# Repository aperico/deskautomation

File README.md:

# Automated Mechanical Desk Lift System

## Quick Start

### Automated Development Pipeline (Recommended)

The fastest way to build and test the project:

```bash
# Complete pipeline: build + dual motor validation + static analysis
python toolchain/run-pipeline.py all

# Build only
python toolchain/run-pipeline.py clean-build

# Run tests (validates both MT_BASIC and MT_ROBUST motor types)
python toolchain/run-pipeline.py test

# Quick unit test during development
python toolchain/run-pipeline.py unit

# Get help
python toolchain/run-pipeline.py help
```

**📖 Detailed Instructions:**
- **Pipeline Guide:** [toolchain/README.md](toolchain/README.md) - Complete pipeline manual
- **Build Guide:** [src/README.md](src/README.md) - Manual build and test instructions
- **Test Overview:** [tests/README.md](tests/README.md) - Test suite quick reference

---

## Project Overview

The Automated Mechanical Desk Lift System is a motorized solution for height-adjustable desks, enabling users to easily switch between sitting and standing positions. The system features responsive controls, safety mechanisms to prevent accidents, and reliable operation over the product lifetime. Key features include:
- **Configurable motor drivers:** Support for both L298N (cost-optimized) and IBT_2 (high-capacity) motor controllers
- Motorized height adjustment from 30 cm to 120 cm
- Support for up to 20 kg load (monitor, keyboard, etc.)
- UP/DOWN buttons for intuitive control
- Immediate halt on button release or obstruction detection
- Robust safety features including limit sensors and current sensing for jam detection
- Smooth, predictable motion for user comfort
- Designed for office environments to improve health and productivity
- Modular architecture for maintainability and future feature expansion
- Comprehensive documentation and testing to ensure quality and reliability
- Open-source hardware and software design for community collaboration and innovation

### Motor Driver Options

The system supports two motor driver configurations, selectable at compile-time:

| Driver | Model | Cost | Capacity | Use Case |
|--------|-------|------|----------|----------|
| **MT_BASIC** | L298N Dual H-Bridge | Low (~$2-5) | Standard (~50kg) | Cost-optimized office desks |
| **MT_ROBUST** | IBT_2 Intelligent Driver | Moderate (~$10-15) | High (~100kg+) | Heavy-duty commercial desks |

Both drivers share the same software (unified HAL interface) and provide equivalent safety and functionality. See [Motor Driver Configuration Guide](documentation/07_MotorDriverConfiguration.md) for build and switching instructions.

## Motor Configuration Architecture

The system implements a robust motor configuration encapsulation pattern to support multiple motor driver types:

### Design Approach

- **Compile-Time Configuration (Current)**: Motor type is defined at compile-time in `src/motor_config.cpp` with validation
- **Runtime-Ready (Future)**: Architecture is prepared for NVM-based runtime configuration without code changes
- **Encapsulation Interface**: `MotorConfig_getMotorType()` function provides the sole accessor for motor configuration
- **Application Transparency**: All application logic is motor-type-agnostic; HAL layer handles driver-specific details

### Configuration Files

| File | Role | Details |
|------|------|---------|
| `src/motor_config.h` | Public interface | Type definitions, feature documentation, function declaration |
| `src/motor_config.cpp` | Private implementation | MOTOR_TYPE macro, validation, getter function, NVM migration comments |

### Switching Motor Drivers

```bash
# Default: MT_BASIC (L298N)
cmake -S . -B build && cmake --build build

# To use MT_ROBUST (IBT_2): Edit src/motor_config.cpp line 44
# #define MOTOR_TYPE MT_BASIC        <- Change to MT_ROBUST
# Then rebuild:
cmake --build build
```

### Test Coverage

All 37 unit and integration tests validate both motor configurations:
- **MT_BASIC**: L298N driver (default)
- **MT_ROBUST**: IBT_2 driver

Tests can be run against either driver by changing the MOTOR_TYPE definition. See [05_SoftwareArchitecture.md](documentation/05_SoftwareArchitecture.md) (AD-009: Motor Configuration Encapsulation) and [06_00_DetailedDesign.md](documentation/06_00_DetailedDesign.md) (Motor Configuration Module) for detailed technical documentation.

---

## Documentation Index

### Development Guidelines

| Document | Description |
|----------|-------------|
| [toolchain/coding_guides_and_checks.md](toolchain/coding_guides_and_checks.md) | **⚠️ Coding standards for safety-critical code (NASA Power of Ten, MISRA C:2012, ISO 25119)** |
| [toolchain/README.md](toolchain/README.md) | Development pipeline and automated testing guide |
| [toolchain/ARCHITECTURE.md](toolchain/ARCHITECTURE.md) | Pipeline architecture and design details |

### Requirements and Design

| Document | Description |
|----------|-------------|
| [01_MissionStatement.md](documentation/01_MissionStatement.md) | Project mission and overall purpose |
| [01_SystemObjectives.md](documentation/01_SystemObjectives.md) | High-level system objectives and goals |
| [02_ConceptOfOperations.md](documentation/02_ConceptOfOperations.md) | Operational concept and use cases |
| [02_01_HARA-prep.md](documentation/02_01_HARA-prep.md) | HARA preparation (draft) |
| [02_02_HARA-complete.md](documentation/02_02_HARA-complete.md) | Hazard analysis and risk assessment (HARA) |
| [02_03_SafetyGoals.md](documentation/02_03_SafetyGoals.md) | Safety goals derived from HARA |
| [03_00_SystemRequirements.md](documentation/03_00_SystemRequirements.md) | System-level requirements specification |
| [03_01_SystemArchitecture.md](documentation/03_01_SystemArchitecture.md) | System architecture and interfaces |
| [03_01_01_TechnicalSafetyConcept.md](documentation/03_01_01_TechnicalSafetyConcept.md) | Technical safety concept |
| [03_02_RequirementsTraceabilityMatrix.md](documentation/03_02_RequirementsTraceabilityMatrix.md) | Requirements traceability matrix |
| [04_SoftwareRequirements.md](documentation/04_SoftwareRequirements.md) | Software requirements and functional specifications |
| [04_01_SoftwareVerificationSpecification.md](documentation/04_01_SoftwareVerificationSpecification.md) | Software test specifications and verification methods |
| [05_SoftwareArchitecture.md](documentation/05_SoftwareArchitecture.md) | Software architecture design and component structure |
| [06_00_DetailedDesign.md](documentation/06_00_DetailedDesign.md) | Detailed software design and implementation details |
| [06_01_DetailedDesign_InteractionDiagrams.md](documentation/06_01_DetailedDesign_InteractionDiagrams.md) | Sequence diagrams and data flow visualizations |
| [07_MotorDriverConfiguration.md](documentation/07_MotorDriverConfiguration.md) | Motor driver configuration guide (L298N vs IBT_2)
| [10_SystemTestSpecification.md](documentation/10_SystemTestSpecification.md) | System test plan and test specifications |
| [10_01_SystemTestReport.md](documentation/10_01_SystemTestReport.md) | System test report and results |
| [11_HardwareDocumentation.md](documentation/11_HardwareDocumentation.md) | Hardware components and wiring documentation |
| [02_ConceptOfOperations_Reviews.md](documentation/02_ConceptOfOperations_Reviews.md) | ConOps review protocol and records |
| [03_00_SystemRequirements_Reviews.md](documentation/03_00_SystemRequirements_Reviews.md) | System requirements review protocol and records |
| [03_01_01_TechnicalSafetyConcept_Reviews.md](documentation/03_01_01_TechnicalSafetyConcept_Reviews.md) | Technical safety concept review protocol and records |
| [03_01_SystemArchitecture_Reviews.md](documentation/03_01_SystemArchitecture_Reviews.md) | System architecture review protocol and records |
| [04_SoftwareRequirements_Reviews.md](documentation/04_SoftwareRequirements_Reviews.md) | Software requirements review protocol and records |
| [05_SoftwareArchitecture_Reviews.md](documentation/05_SoftwareArchitecture_Reviews.md) | Software architecture review protocol and records |
| [06_DetailedDesign_Reviews.md](documentation/06_DetailedDesign_Reviews.md) | Detailed design review protocol and records |
| [10_SystemTestSpecification_Reviews.md](documentation/10_SystemTestSpecification_Reviews.md) | System test specification review protocol and records |
| [feature-pdrs/](documentation/feature-pdrs/) | System feature concept reviews |

## Project Structure

### Root Directory

| File/Directory | Description |
|----------------|-------------|
| `CMakeLists.txt` | CMake build configuration file |
| `CMakePresets.json` | CMake preset configurations |
| `README.md` | Project overview and instructions (this file) |
| `.github/` | GitHub workflows and CI/CD configuration |

### Source Code (`src/`)

| File | Description |
|------|-------------|
| `desk_app.cpp/h` | Main application logic and state machine |
| `desk_types.h` | Type definitions and data structures |
| `hal.cpp/h` | Hardware Abstraction Layer (HAL) interface |
| `motor_config.h` | Motor driver type configuration (MT_BASIC or MT_ROBUST) |
| `motor_controller.cpp/h` | Motor control logic and algorithms |
| `pin_config.h` | Arduino pin assignments (configurable per motor type) |
| `src.ino` | Arduino firmware entry point |

### Tests (`tests/`)

| File | Description |
|------|-------------|
| `UnitTests.cpp` | Unit tests for individual functions and classes |
| `ComponentTests.cpp` | Component-level integration tests |
| `IntegrationTests.cpp` | Full system integration tests |
| `hal_mock/` | Mock implementations of HAL for testing on host |
| `└── HALMock.cpp/h` | Mock HAL implementation |
| `└── SerialMock.cpp/h` | Mock Serial communication for testing |

### Training Materials (`00_training_context/`)

| File | Description |
|------|-------------|
| `00_agenda.md` | Training overview and agenda |
| `01_hello-world.md` | Getting started guide |
| `02_aisetup.md` | AI/Copilot setup instructions |
| `03_prompting-techniques.md` | AI prompting best practices |
| `04_00_deskautomation-syseng.md` | Systems engineering overview |
| `04_01_00_system-definition.md` | System definition guide |
| `04_01_01_system-definition-architecture.md` | Architecture definition guide |
| `04_02_software-construction.md` | Software construction practices |
| `04_03_00_component-verification.md` | Component testing guide |
| `04_03_01_software_integration-verification.md` | Integration testing guide |
| `04_03_03_system-testing.md` | System testing guide |
| `05_traceability-matrix.md` | Requirements traceability |
| `06_workflow-pipelines.md` | CI/CD pipeline documentation |
| `07_process-assessment.md` | Process quality assessment |

### Schematics (`schematics/`)

| Directory | Description |
|-----------|-------------|
| `schmatics_desk_automation/` | KiCad project files for desk automation |
| `└── DeskAutomation_MotorControl/` | Motor control circuit schematics |
| `└── DeskAutomation.pretty/` | Custom KiCad footprints |

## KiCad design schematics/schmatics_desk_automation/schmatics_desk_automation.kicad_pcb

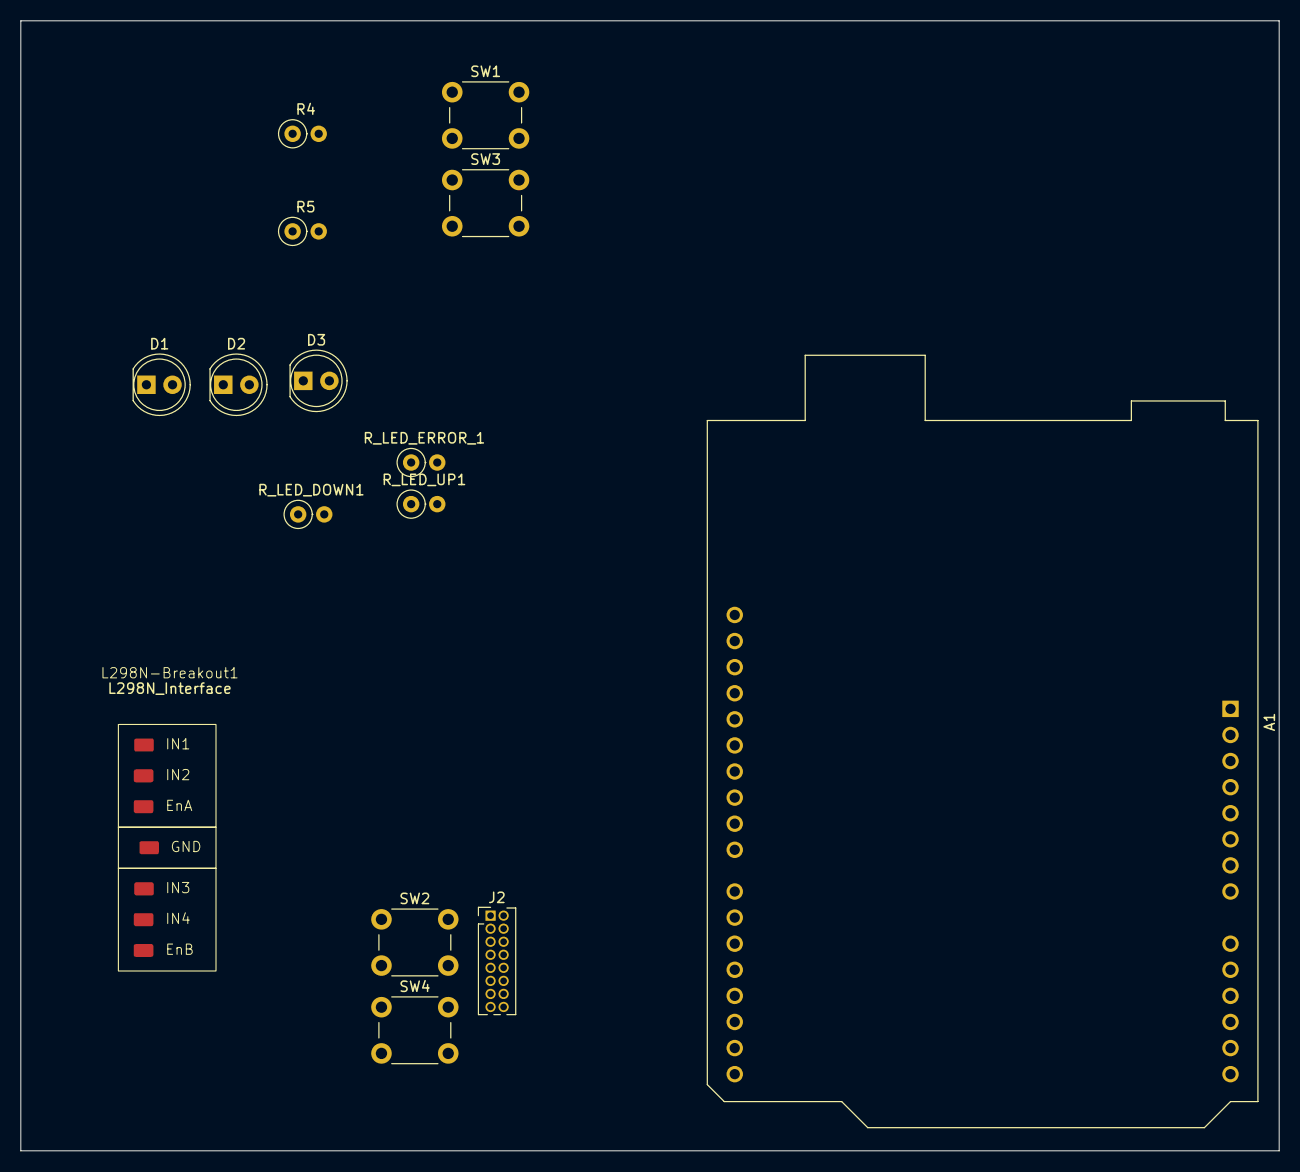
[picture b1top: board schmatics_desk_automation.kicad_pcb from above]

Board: 2 copper layers, 122.5 x 110.0 mm, 15 parts (0 on the bottom side), 16 nets, no tracks yet.

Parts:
A1: Arduino_UNO_R3
D1: LED_DOWN; LED_D5.0mm
D2: LED UP; LED_D5.0mm
D3: ERROR_LED; LED_D5.0mm
J2: Conn_01x15_MountingPin; PinHeader_2x08_P1.27mm_Vertical
L298N-Breakout1: L298N_Interface; L298N Interface
R4, R5: 330; R_Axial_DIN0207_L6.3mm_D2.5mm_P2.54mm_Vertical
R_LED_DOWN1: 330; R_Axial_DIN0207_L6.3mm_D2.5mm_P2.54mm_Vertical
R_LED_ERROR_1: 330; R_Axial_DIN0207_L6.3mm_D2.5mm_P2.54mm_Vertical
R_LED_UP1: 330; R_Axial_DIN0207_L6.3mm_D2.5mm_P2.54mm_Vertical
SW1: BT_UP; SW_PUSH_6mm_H5mm
SW2: Lower Limit; SW_PUSH_6mm_H5mm
SW3: BT_DOWN; SW_PUSH_6mm_H5mm
SW4: Uppr Limit; SW_PUSH_6mm_H5mm

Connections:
Button DOWN: A1.18 (D3), J2.8, SW3.1
Button UP: A1.17 (D2), J2.9, SW1.1
GND: D1.2 (A), D2.2 (A), D3.2 (A), J2.1, J2.2, L298N-Breakout1.4, R4.2, R5.2, R_LED_ERROR_1.1, SW2.2, SW4.2
LED_DOWN: A1.25 (D10), J2.4, R_LED_DOWN1.1
LED_ERROR: A1.7 (GND), A1.28 (D13)
LED_UP: A1.26 (D11), J2.3, R_LED_UP1.1
Lower Limit: J2.10, SW2.1
Motor DIR CTRL 1: A1.20 (D5), J2.7, L298N-Breakout1.1
Motor DIR CTRL 2: A1.21 (D6), J2.6, L298N-Breakout1.2
Motor PWM: A1.24 (D9), J2.5, L298N-Breakout1.3
unnamed: D1.1 (K), R_LED_DOWN1.2
unnamed: D2.1 (K), R_LED_UP1.2
unnamed: D3.1 (K), R_LED_ERROR_1.2
unnamed: R4.1, SW1.2
unnamed: R5.1, SW3.2
Uppler Limit: J2.11, SW4.1

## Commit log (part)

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2025-12-29 feat: Implement initial application logic, state machine, and hardware abstraction layer for desk automation.
2025-12-29 feat: Establish initial project structure, CMake build system, HAL, desk controller logic, and Google Test setup.
2025-12-29 feat: Initialize application state and enhance HAL with state processing for desk automation
2025-12-29 chore: Remove obsolete InstallationLog.txt file
2025-12-30 feat: Refactor HAL and PinConfig for improved LED handling and state management
2025-12-30 feat: Revise README for improved clarity, structure, and detail on system architecture and use cases
2026-01-06 Implement enhanced error handling and dual button logic in DeskController
    - Added error state handling for simultaneous activation of both upper and lower limits.
    - Implemented emergency stop logic when moving up or down while a limit is active.
    - Updated button press logic to prevent movement when both UP and DOWN buttons are pressed.
    - Enhanced unit tests to cover new error handling scenarios and button press logic.
    - Removed redundant code and improved readability in DeskController and unit tests.
2026-01-07 Refactor documentation: Remove Software Requirements, add new files for Glossary, Hardware Connections, Roadmap, Safety Notes, Software Architecture, Software Detailed Design, Software Test Cases Spe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
    - Deleted SoftwareRequirements.md and replaced with a new version.
    - Introduced Glossary.md to define key terms.
    - Added HardwareConnections.md for pin assignments.
    - Created Roadmap.md outlining planned enhancements.
    - Included SafetyNotes.md for safety precautions.
    - Developed SoftwareArchitecture.md detailing system structure.
2026-01-07 Refactor documentation: Revise README, enhance safety notes, and update glossary, hardware connections, roadmap, and software architecture for clarity and completeness
2026-01-07 Refactor documentation: Update navigation links and enhance glossary for improved clarity and organization
2026-01-07 Refactor documentation: Enhance README with a glossary and improve navigation in Software Architecture and Software Detailed Design for clarity and organization
2026-01-07 Refactor documentation: Consolidate glossary content into README, update hardware connections references, and enhance compliance details across multiple documents for clarity and consistency
2026-01-07 Refactor README and add ASPICE Assessment: Enhance documentation index with detailed descriptions and introduce a comprehensive ASPICE assessment checklist for improved compliance tracking and clarit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
2026-01-07 Refactor ASPICE Assessment: Add introductory section for overall maturity classification to enhance clarity and context for compliance evaluation.
2026-01-07 Refactor README: Remove outdated documentation index and streamline ASPICE maturity level description for improved clarity and focus.
2026-01-07 Refactor README: Add documentation index with links and descriptions for improved navigation and clarity
2026-01-07 Add desk crank image to README for enhanced visual representation
2026-01-07 Refactor CI workflow: Clean up GoogleTest installation steps for improved clarity
2026-01-07 Enhance CI workflow: Add Cppcheck linting step and report upload for improved code quality
2026-01-07 Refactor CI workflow: Update coverage report generation to use geninfo for improved accuracy
2026-01-07 Fix image file extension in README.md for correct display
2026-01-07 Fix unit test output handling in CI workflow to correctly generate JUnit XML report
2026-01-07 Refactor Software Detailed Design and System Use Cases
    - Updated Software Detailed Design document for clarity and consistency, including improved formatting and organization of sections.
    - Enhanced module decomposition details and added comprehensive descriptions for each module.
    - Revised System Use Cases to include a new use case diagram and detailed flows for each use case, ensuring alignment with the updated design.
    - Improved error handling and safety features in use cases, emphasizing user interactions and system responses.
    - Added functional coverage map linking core functions to relevant use cases.
    - Made minor adjustments to the main Arduino file to ensure proper static declaration
2026-01-07 Enhance integration testing framework: Add IntegrationTests.cpp, improve HAL mock implementations, and update documentation for test specifications and traceability matrix.
2026-01-07 Refactor CI workflow: Update test execution to run only Unit and Integration labelled tests, and adjust result file naming for clarity.
2026-01-07 Update ASPICE maturity assessment: Revise document structure, enhance clarity, and update evaluation results and action plans.
2026-01-07 Enhance System Use Cases Documentation
    - Updated document version to 1.1 and added last updated date, status, author, and reviewers.
    - Added an overview section to clarify the purpose of the document.
    - Introduced a use case summary table for quick reference of all use cases, including ID, name, priority, frequency, status, and related requirements.
    - Expanded individual use cases (UC-01 to UC-08) with detailed descriptions, triggers, preconditions, main flows, alternative flows, exception flows, postconditions, related requirements, and test ca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
    - Improved formatting for better readability and adherence to IEEE 29148-2018 standard.
2026-01-07 feat: Implement movement timeout and enhance state management
    - Added movement timeout functionality (SWE-REQ-018) to prevent prolonged motor operation.
    - Updated DeskController to track movement start time and enforce a 30-second timeout.
    - Enhanced state transitions to ensure safe operation during simultaneous button presses and limit switch activations.
    - Improved logging capabilities in HAL with optional logger support.
    - Refactored HAL initialization and added startup wait functionality for hardware stabilization.
    - Updated integration and software tests to cover new timeout and state transition scenarios.
2026-01-07 feat: Add white-box testing interface and unit tests for DeskController functionality
2026-01-10 Add L298N interface library and enhance desk controller functionality
    - Created a new symbol library for L298N interface in KiCad.
    - Added autosave lock file for schematic design.
    - Improved DeskController logic to handle error recovery from limit switches.
    - Updated HAL initialization to set pin modes for upper and lower limit switches.
    - Modified pin configuration for error LED and added definitions for limit switch inputs.
    - Enhanced main loop to read limit switch states and integrate them into the application logic.
2026-01-19 Refactor integration and unit tests for IBT-2 hardware
    - Simplified IntegrationTests.cpp by removing extensive user input and LED tests, focusing on core functionality.
    - Added new tests for switch states (OFF, UP, DOWN) in SoftwareTests.cpp to validate motor outputs.
    - Updated UnitTests.cpp to reflect minimal test cases for switch states, removing unnecessary complexity.
    - Introduced a new binary executable for desk tests.
2026-01-19 Refactor integration tests for DeskController and HAL; remove minimal software tests
    - Expanded IntegrationTests.cpp to include comprehensive integration tests for DeskController and HAL, covering various states, transitions, and interface contracts.
    - Removed SoftwareTests.cpp as it contained minimal tests that are now covered by the integration tests.
    - Updated UnitTests.cpp to follow a consistent naming convention for unit tests.
    - Deleted the outdated desk_tests.exe binary.
2026-01-19 Enhance CI/CD pipeline: unify test execution and add Cppcheck installation instructions
2026-01-19 Update .gitignore to exclude cppcheck-addons.zip and enhance README with local CI pipeline instructions
2026-01-19 Improve cppcheck addon handling: skip extraction and download if already present
2026-01-19 Enhance Cppcheck integration: fetch and use addons if not present
2026-01-19 Add error handling for PR comment creation in CI workflow
2026-01-19 Remove unused core module import in quality report script
2026-01-19 Enhance cppcheck addon fetching: improve caching, extraction, and verification of addon files
2026-01-19 Enhance cppcheck addon fetching: implement stable release download and improved extraction handling
2026-01-19 Enhance cppcheck workflow: allow continuation on error and improve addon fetching script for Linux compatibility
2026-01-19 Enhance dynamic analysis workflow: add error handling and placeholder creation for AddressSanitizer, Valgrind, and performance profiling steps
2026-01-19 Refactor cppcheck integration: remove CERT checks and update related scripts for streamlined static analysis
2026-01-19 Refactor code structure for improved readability and maintainability
2026-01-19 Refactor System Integration Tests: rename fixture class for consistency
2026-01-19 Refactor integration and unit tests: rename HALIntegrationTests to HALIntegration and DeskControllerStateHandlerTest to DeskControllerUnit for consistency
2026-01-19 Refactor HAL integration test case: update naming convention, enhance documentation, and improve test structure for motor control verification
2026-01-25 Refactor tests and remove deprecated files
    - Deleted DeskControllerTestInterface.h as it is no longer needed.
    - Updated IntegrationTests.cpp to focus on HAL and system integration tests, removing user input and LED tests.
    - Removed SoftwareTests.cpp as it contained redundant tests.
    - Expanded UnitTests.cpp to include comprehensive motor controller unit tests, covering initialization, ramping, direction changes, and stop commands.
    - Added HALMock files to simulate Arduino environment for unit testing, including mock implementations for pin control and serial communication.
    - Removed the old desk_tests.exe binary as it is no longer relevant.
2026-01-25 feat: Add comprehensive hardware documentation for desk automation components
2026-01-26 feat: Update documentation and add local development pipeline script for desk automation
2026-01-26 feat: Update mission statement document to reflect version changes, implementation details, and testing status
2026-01-26 feat: Enhance CMake configuration and pipeline scripts for improved performance and diagnostics
2026-01-27 refactor: Update LED blink example to use a simpler timing mechanism and pin configuration
2026-02-12 feat: Add Software Requirements Review Protocol documentation
2026-02-21 refactor: Revise Software Requirements Review Protocol for clarity and structure
2026-02-21 chore: Update document metadata across multiple specifications for versioning and approval status
2026-02-21 Add System Test Specification Review Protocol and Source Code Build & Test Guide
    - Created a new document for the System Test Specification Review Protocol to ensure quality standards are met during reviews.
    - Added detailed instructions for building and testing the Automated Mechanical Desk Lift System, including prerequisites, build commands, and CI/CD pipeline usage.
2026-02-21 feat: Add project overview and key features to README
2026-02-21 fix: Update motor fault timer initialization and handling for clarity
2026-02-22 Add static analysis rules and pipeline script
    - Implemented various static analysis rules to enforce coding standards:
    - RULE-001: No goto statements
    - RULE-002: No setjmp/longjmp
    - RULE-007: No while(true)/for(;;) except main
    - RULE-009: No malloc/calloc/realloc/free
    - RULE-011: Stack usage per function <= 512 bytes
2026-02-22 fix: Include stddef.h for NULL definition and initialize MotorControllerOutput_t with empty braces
2026-02-22 Refactor code quality metrics and MISRA rules
    - Updated source paths in log files to reflect new workspace structure.
    - Adjusted timestamps in log files for consistency.
    - Added new rules for function length, parameter count, nesting depth, file length, and assertion density.
    - Enhanced existing rules with AI-generated comments for clarity.
    - Removed redundant rules and ensured proper categorization in summary documentation.
    - Improved regex patterns for parameter counting and nesting depth analysis.
2026-02-22 feat: Add automation scripts for MISRA compliance and code quality checks
